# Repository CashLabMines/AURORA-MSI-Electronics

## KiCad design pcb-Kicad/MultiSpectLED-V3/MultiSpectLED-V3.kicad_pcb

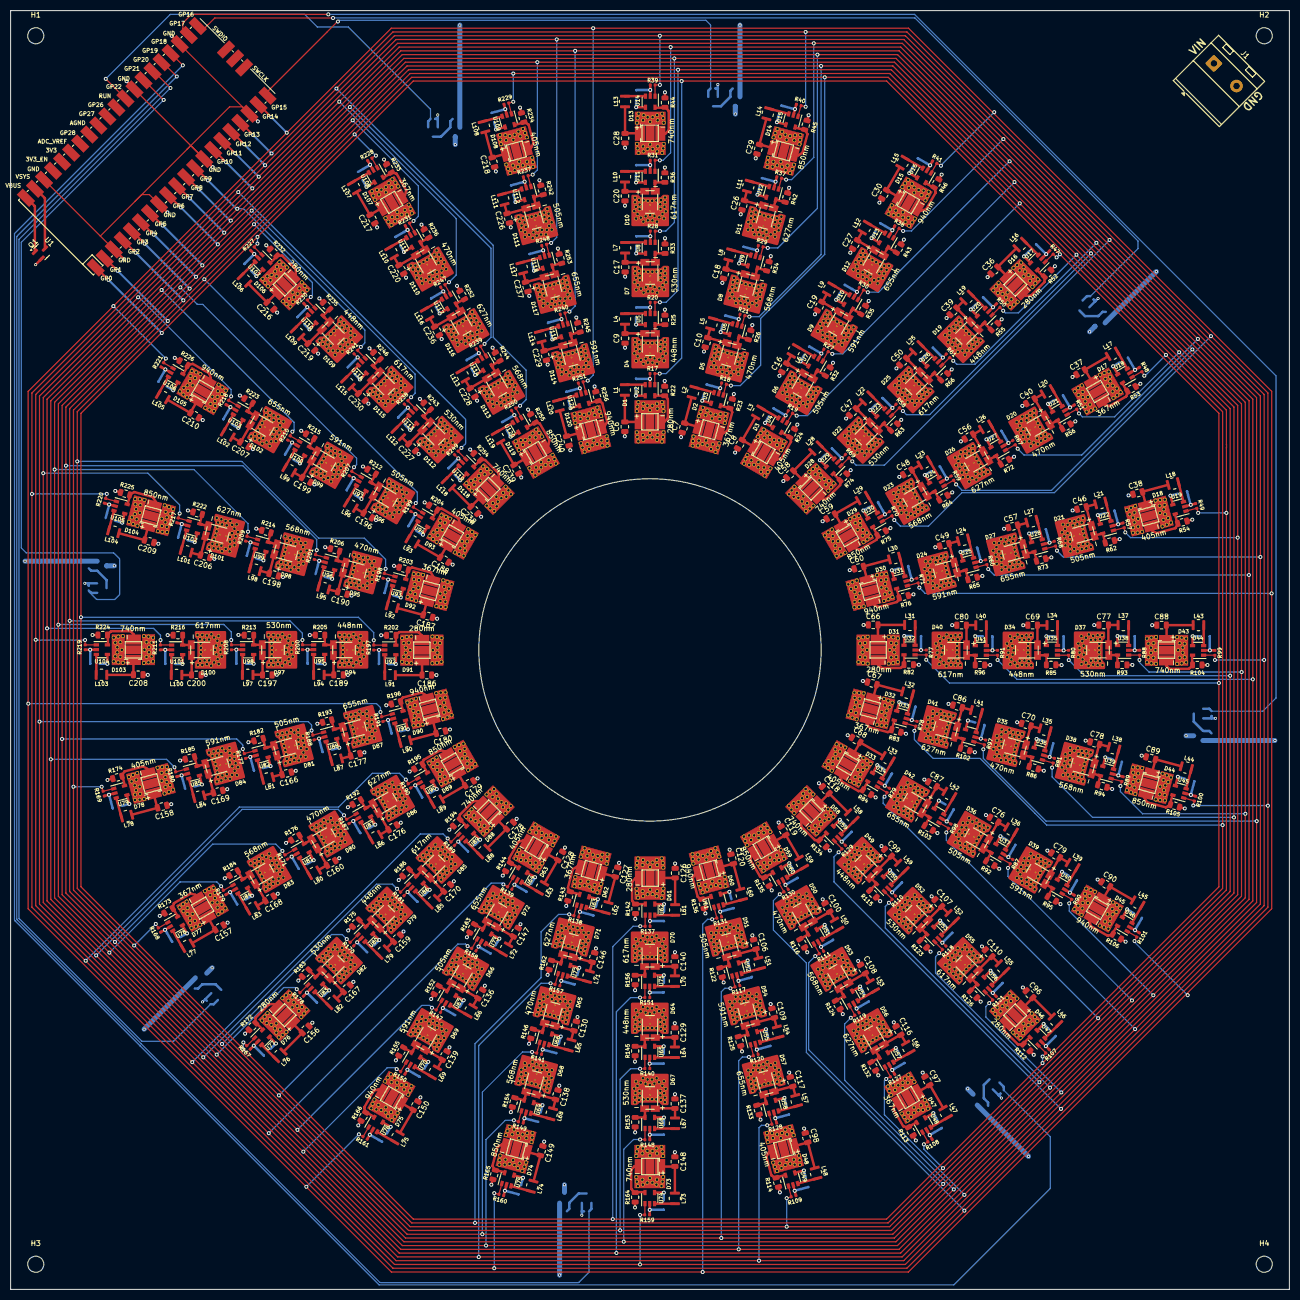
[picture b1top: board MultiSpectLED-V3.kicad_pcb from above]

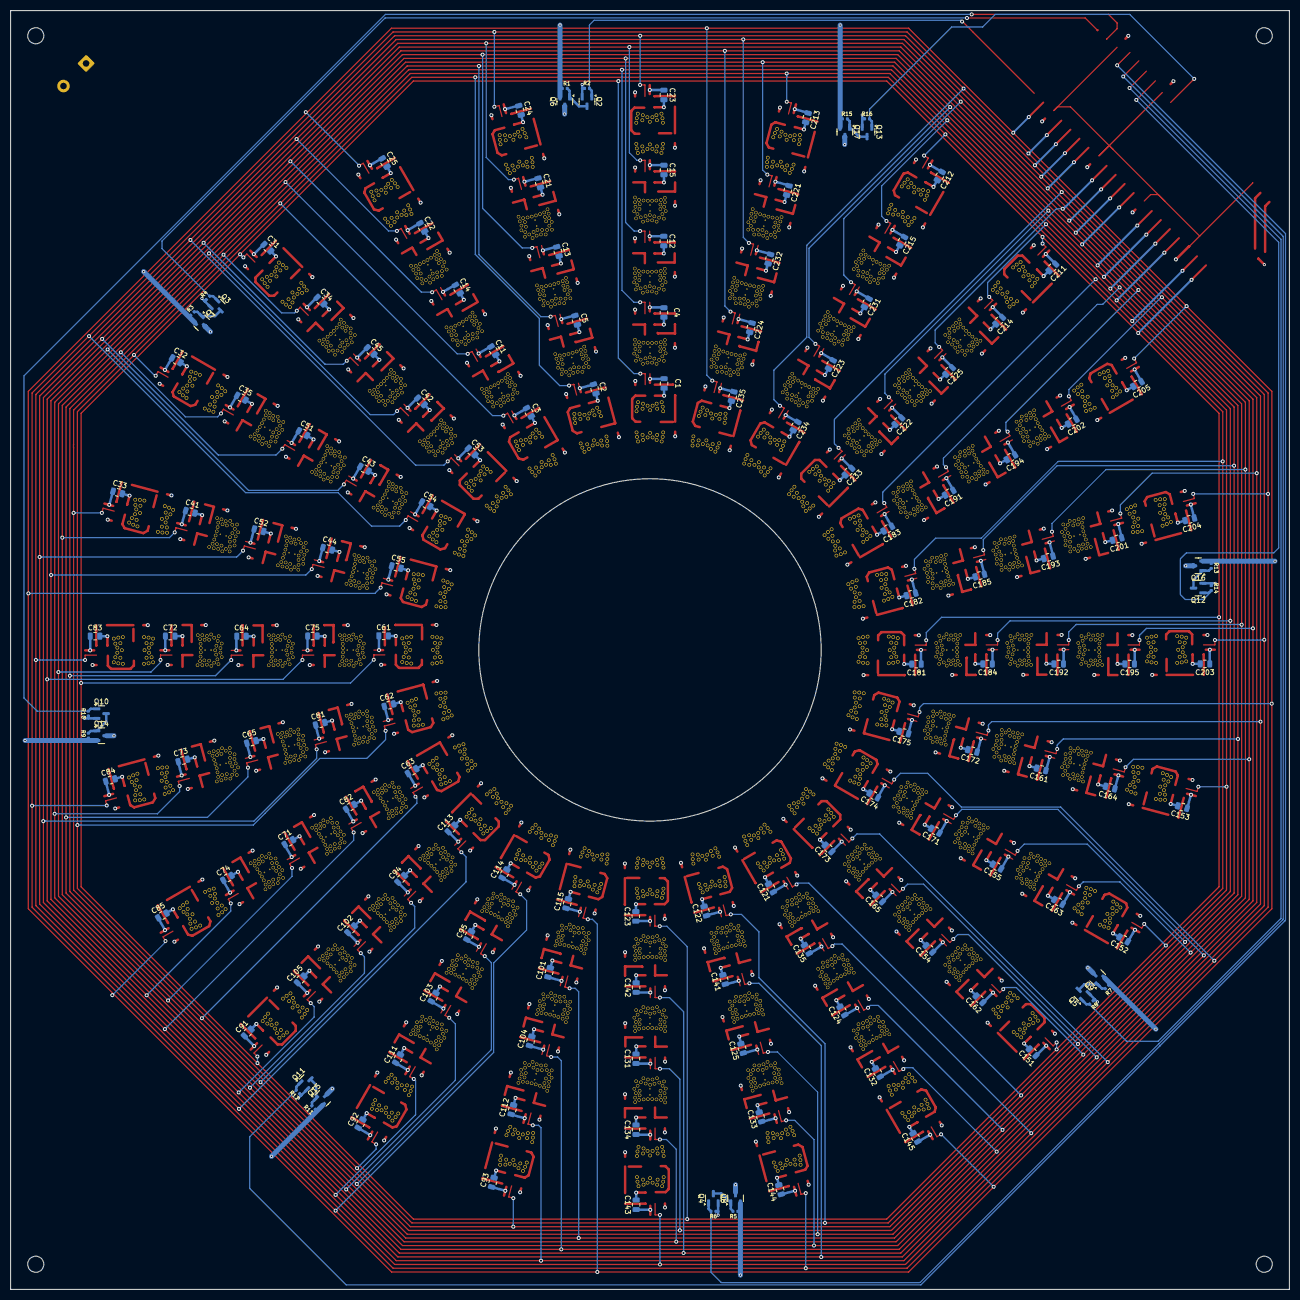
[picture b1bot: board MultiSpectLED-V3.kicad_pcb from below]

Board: 4 copper layers, 254.0 x 254.0 mm, 879 parts (152 on the bottom side), 403 nets.

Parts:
C1, C2, C3, C4, C5, C11, C12, C13, C14, C15, C21, C22, C23, C24, C25, C31, C32, C33, C34, C35, C41, C42, C43, C44, C45, C51, C52, C53, C54, C55, C61, C62, C63, C64, C65, C71, C72, C73, C74, C75, C81, C82, C83, C84, C85, C91, C92, C93, C94, C95, C101, C102, C103, C104, C105, C111, C112, C113, C114, C115, C121, C122, C123, C124, C125, C131, C132, C133, C134, C135, C141, C142, C143, C144, C145, C151, C152, C153, C154, C155, C161, C162, C163, C164, C165, C171, C172, C173, C174, C175, C181, C182, C183, C184, C185, C191, C192, C193, C194, C195, C201, C202, C203, C204, C205, C211, C212, C213, C214, C215, C221, C222, C223, C224, C225, C231, C232, C233, C234, C235: 10uF; C_0805_2012Metric
C6, C7, C8, C9, C10, C16, C17, C18, C19, C20, C26, C27, C28, C29, C30, C36, C37, C38, C39, C40, C46, C47, C48, C49, C50, C56, C57, C58, C59, C60, C66, C67, C68, C69, C70, C76, C77, C78, C79, C80, C86, C87, C88, C89, C90, C96, C97, C98, C99, C100, C106, C107, C108, C109, C110, C116, C117, C118, C119, C120, C126, C127, C128, C129, C130, C136, C137, C138, C139, C140, C146, C147, C148, C149, C150, C156, C157, C158, C159, C160, C166, C167, C168, C169, C170, C176, C177, C178, C179, C180, C186, C187, C188, C189, C190, C196, C197, C198, C199, C200, C206, C207, C208, C209, C210, C216, C217, C218, C219, C220, C226, C227, C228, C229, C230, C236, C237, C238, C239, C240: 1uF; C_0805_2012Metric
D1, D16, D31, D46, D61, D76, D91, D106: 280nm; Luminus_XBT3535
D2, D17, D32, D47, D62, D77, D92, D107: 367nm; SeoulViosys_CUN6GF1A
D3, D18, D33, D48, D63, D78, D93, D108: 405nm; Everlight_ELUA3535
D4, D19, D34, D49, D64, D79, D94, D109: 448nm; LuxeonRebelColor
D5, D20, D35, D50, D65, D80, D95, D110: 470nm; LuxeonRebelColor
D6, D21, D36, D51, D66, D81, D96, D111: 505nm; LuxeonRebelColor
D7, D22, D37, D52, D67, D82, D97, D112: 530nm; LuxeonRebelColor
D8, D23, D38, D53, D68, D83, D98, D113: 568nm; LuxeonRebelColor
D9, D24, D39, D54, D69, D84, D99, D114: 591nm; LuxeonRebelColor
D10, D25, D40, D55, D70, D85, D100, D115: 617nm; LuxeonRebelColor
D11, D26, D41, D56, D71, D86, D101, D116: 627nm; LuxeonRebelColor
D12, D27, D42, D57, D72, D87, D102, D117: 655nm; LuxeonRebelColor
D13, D28, D43, D58, D73, D88, D103, D118: 740nm; QT_Brightek_QBHP684
D14, D29, D44, D59, D74, D89, D104, D119: 850nm; QT_Brightek_QBHP684
D15, D30, D45, D60, D75, D90, D105, D120: 940nm; QT_Brightek_QBHP684
H1, H2, H3, H4: M3 Mounting Hole; MountingHole_3.2mm_M3
J1: Screw_Terminal_01x02; TerminalBlock_MetzConnect_Type701_RT11L02HGLU_1x02_P6.35mm_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
L1, L2, L3, L4, L5, L6, L7, L8, L9, L10, L11, L12, L13, L14, L15, L16, L17, L18, L19, L20, L21, L22, L23, L24, L25, L26, L27, L28, L29, L30, L31, L32, L33, L34, L35, L36, L37, L38, L39, L40, L41, L42, L43, L44, L45, L46, L47, L48, L49, L50, L51, L52, L53, L54, L55, L56, L57, L58, L59, L60, L61, L62, L63, L64, L65, L66, L67, L68, L69, L70, L71, L72, L73, L74, L75, L76, L77, L78, L79, L80, L81, L82, L83, L84, L85, L86, L87, L88, L89, L90, L91, L92, L93, L94, L95, L96, L97, L98, L99, L100, L101, L102, L103, L104, L105, L106, L107, L108, L109, L110, L111, L112, L113, L114, L115, L116, L117, L118, L119, L120: 4.7u; L_1007_2518Metric
Q1, Q6, Q7, Q8, Q9, Q14, Q15, Q16, Q17: DMG2301L; SOT-23
Q2, Q3, Q4, Q5, Q10, Q11, Q12, Q13: BC817; SOT-23
R1, R2, R3, R4, R5, R6, R7, R8, R9, R10, R11, R12, R13, R14, R15, R16, R17, R18, R19, R20, R21, R27, R28, R29, R30, R31, R37, R38, R39, R40, R41, R47, R48, R49, R50, R51, R57, R58, R59, R60, R61, R67, R68, R69, R70, R71, R77, R78, R79, R80, R81, R87, R88, R89, R90, R91, R97, R98, R99, R100, R101, R107, R108, R109, R110, R111, R117, R118, R119, R120, R121, R127, R128, R129, R130, R131, R137, R138, R139, R140, R141, R147, R148, R149, R150, R151, R157, R158, R159, R160, R161, R167, R168, R169, R170, R171, R177, R178, R179, R180, R181, R187, R188, R189, R190, R191, R197, R198, R199, R200, R201, R207, R208, R209, R210, R211, R217, R218, R219, R220, R221, R227, R228, R229, R230, R231, R237, R238, R239, R240, R241, R247, R248, R249, R250, R251: 100K; R_0402_1005Metric
R22, R23, R24, R25, R26, R32, R33, R34, R35, R36, R42, R43, R44, R45, R46, R52, R53, R54, R55, R56, R62, R63, R64, R65, R66, R72, R73, R74, R75, R76, R82, R83, R84, R85, R86, R92, R93, R94, R95, R96, R102, R103, R104, R105, R106, R112, R113, R114, R115, R116, R122, R123, R124, R125, R126, R132, R133, R134, R135, R136, R142, R143, R144, R145, R146, R152, R153, R154, R155, R156, R162, R163, R164, R165, R166, R172, R173, R174, R175, R176, R182, R183, R184, R185, R186, R192, R193, R194, R195, R196, R202, R203, R204, R205, R206, R212, R213, R214, R215, R216, R222, R223, R224, R225, R226, R232, R233, R234, R235, R236, R242, R243, R244, R245, R246, R252, R253, R254, R255, R256: 0.2; R_0805_2012Metric
U1: RaspberryPi_Pico2_SM; RPi_Pico_SMD_SM
U2, U3, U4, U5, U6, U7, U8, U9, U10, U11, U12, U13, U14, U15, U16, U17, U18, U19, U20, U21, U22, U23, U24, U25, U26, U27, U28, U29, U30, U31, U32, U33, U34, U35, U36, U37, U38, U39, U40, U41, U42, U43, U44, U45, U46, U47, U48, U49, U50, U51, U52, U53, U54, U55, U56, U57, U58, U59, U60, U61, U62, U63, U64, U65, U66, U67, U68, U69, U70, U71, U72, U73, U74, U75, U76, U77, U78, U79, U80, U81, U82, U83, U84, U85, U86, U87, U88, U89, U90, U91, U92, U93, U94, U95, U96, U97, U98, U99, U100, U101, U102, U103, U104, U105, U106, U107, U108, U109, U110, U111, U112, U113, U114, U115, U116, U117, U118, U119, U120, U121: PAM2804; SOT-23-5

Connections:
+5V: J1.1, Q1.2 (S), Q6.2 (S), Q7.2 (S), Q8.2 (S), Q9.2 (S), Q14.2 (S), Q15.2 (S), Q16.2 (S), Q17.2 (S), R1.1, R3.1, R5.1, R7.1, R9.1, R11.1, R13.1, R15.1
/LED Column 1/VCC: C1.2, C2.2, C3.2, C4.2, C5.2, C11.2, C12.2, C13.2, C14.2, C15.2, C21.2, C22.2, C23.2, C24.2, C25.2, Q6.3 (D), U2.4 (VIN), U3.4 (VIN), U4.4 (VIN), U5.4 (VIN), U6.4 (VIN), U7.4 (VIN), U8.4 (VIN), U9.4 (VIN), U10.4 (VIN), U11.4 (VIN), U12.4 (VIN), U13.4 (VIN), U14.4 (VIN), U15.4 (VIN), U16.4 (VIN)
/LED Column 2/VCC: C31.2, C32.2, C33.2, C34.2, C35.2, C41.2, C42.2, C43.2, C44.2, C45.2, C51.2, C52.2, C53.2, C54.2, C55.2, Q7.3 (D), U17.4 (VIN), U18.4 (VIN), U19.4 (VIN), U20.4 (VIN), U21.4 (VIN), U22.4 (VIN), U23.4 (VIN), U24.4 (VIN), U25.4 (VIN), U26.4 (VIN), U27.4 (VIN), U28.4 (VIN), U29.4 (VIN), U30.4 (VIN), U31.4 (VIN)
/LED Column 3/VCC: C61.2, C62.2, C63.2, C64.2, C65.2, C71.2, C72.2, C73.2, C74.2, C75.2, C81.2, C82.2, C83.2, C84.2, C85.2, Q14.3 (D), U32.4 (VIN), U33.4 (VIN), U34.4 (VIN), U35.4 (VIN), U36.4 (VIN), U37.4 (VIN), U38.4 (VIN), U39.4 (VIN), U40.4 (VIN), U41.4 (VIN), U42.4 (VIN), U43.4 (VIN), U44.4 (VIN), U45.4 (VIN), U46.4 (VIN)
/LED Column 4/VCC: C91.2, C92.2, C93.2, C94.2, C95.2, C101.2, C102.2, C103.2, C104.2, C105.2, C111.2, C112.2, C113.2, C114.2, C115.2, Q15.3 (D), U47.4 (VIN), U48.4 (VIN), U49.4 (VIN), U50.4 (VIN), U51.4 (VIN), U52.4 (VIN), U53.4 (VIN), U54.4 (VIN), U55.4 (VIN), U56.4 (VIN), U57.4 (VIN), U58.4 (VIN), U59.4 (VIN), U60.4 (VIN), U61.4 (VIN)
/LED Column 5/VCC: C121.2, C122.2, C123.2, C124.2, C125.2, C131.2, C132.2, C133.2, C134.2, C135.2, C141.2, C142.2, C143.2, C144.2, C145.2, Q8.3 (D), U62.4 (VIN), U63.4 (VIN), U64.4 (VIN), U65.4 (VIN), U66.4 (VIN), U67.4 (VIN), U68.4 (VIN), U69.4 (VIN), U70.4 (VIN), U71.4 (VIN), U72.4 (VIN), U73.4 (VIN), U74.4 (VIN), U75.4 (VIN), U76.4 (VIN)
/LED Column 6/VCC: C151.2, C152.2, C153.2, C154.2, C155.2, C161.2, C162.2, C163.2, C164.2, C165.2, C171.2, C172.2, C173.2, C174.2, C175.2, Q9.3 (D), U77.4 (VIN), U78.4 (VIN), U79.4 (VIN), U80.4 (VIN), U81.4 (VIN), U82.4 (VIN), U83.4 (VIN), U84.4 (VIN), U85.4 (VIN), U86.4 (VIN), U87.4 (VIN), U88.4 (VIN), U89.4 (VIN), U90.4 (VIN), U91.4 (VIN)
/LED Column 7/VCC: C181.2, C182.2, C183.2, C184.2, C185.2, C191.2, C192.2, C193.2, C194.2, C195.2, C201.2, C202.2, C203.2, C204.2, C205.2, Q16.3 (D), U92.4 (VIN), U93.4 (VIN), U94.4 (VIN), U95.4 (VIN), U96.4 (VIN), U97.4 (VIN), U98.4 (VIN), U99.4 (VIN), U100.4 (VIN), U101.4 (VIN), U102.4 (VIN), U103.4 (VIN), U104.4 (VIN), U105.4 (VIN), U106.4 (VIN)
/LED Column 8/VCC: C211.2, C212.2, C213.2, C214.2, C215.2, C221.2, C222.2, C223.2, C224.2, C225.2, C231.2, C232.2, C233.2, C234.2, C235.2, Q17.3 (D), U107.4 (VIN), U108.4 (VIN), U109.4 (VIN), U110.4 (VIN), U111.4 (VIN), U112.4 (VIN), U113.4 (VIN), U114.4 (VIN), U115.4 (VIN), U116.4 (VIN), U117.4 (VIN), U118.4 (VIN), U119.4 (VIN), U120.4 (VIN), U121.4 (VIN)
/PWM_280nm: R17.1, R47.1, R77.1, R107.1, R137.1, R167.1, R197.1, R227.1, U1.1 (GPIO0), U2.1 (EN), U17.1 (EN), U32.1 (EN), U47.1 (EN), U62.1 (EN), U77.1 (EN), U92.1 (EN), U107.1 (EN)
/PWM_367nm: R18.1, R48.1, R78.1, R108.1, R138.1, R168.1, R198.1, R228.1, U1.2 (GPIO1), U3.1 (EN), U18.1 (EN), U33.1 (EN), U48.1 (EN), U63.1 (EN), U78.1 (EN), U93.1 (EN), U108.1 (EN)
/PWM_405nm: R19.1, R49.1, R79.1, R109.1, R139.1, R169.1, R199.1, R229.1, U1.4 (GPIO2), U4.1 (EN), U19.1 (EN), U34.1 (EN), U49.1 (EN), U64.1 (EN), U79.1 (EN), U94.1 (EN), U109.1 (EN)
/PWM_448nm: R20.1, R50.1, R80.1, R110.1, R140.1, R170.1, R200.1, R230.1, U1.5 (GPIO3), U5.1 (EN), U20.1 (EN), U35.1 (EN), U50.1 (EN), U65.1 (EN), U80.1 (EN), U95.1 (EN), U110.1 (EN)
/PWM_470nm: R21.1, R51.1, R81.1, R111.1, R141.1, R171.1, R201.1, R231.1, U1.6 (GPIO4), U6.1 (EN), U21.1 (EN), U36.1 (EN), U51.1 (EN), U66.1 (EN), U81.1 (EN), U96.1 (EN), U111.1 (EN)
/PWM_505nm: R27.1, R57.1, R87.1, R117.1, R147.1, R177.1, R207.1, R237.1, U1.7 (GPIO5), U7.1 (EN), U22.1 (EN), U37.1 (EN), U52.1 (EN), U67.1 (EN), U82.1 (EN), U97.1 (EN), U112.1 (EN)
/PWM_530nm: R28.1, R58.1, R88.1, R118.1, R148.1, R178.1, R208.1, R238.1, U1.9 (GPIO6), U8.1 (EN), U23.1 (EN), U38.1 (EN), U53.1 (EN), U68.1 (EN), U83.1 (EN), U98.1 (EN), U113.1 (EN)
/PWM_568nm: R29.1, R59.1, R89.1, R119.1, R149.1, R179.1, R209.1, R239.1, U1.10 (GPIO7), U9.1 (EN), U24.1 (EN), U39.1 (EN), U54.1 (EN), U69.1 (EN), U84.1 (EN), U99.1 (EN), U114.1 (EN)
/PWM_591nm: R30.1, R60.1, R90.1, R120.1, R150.1, R180.1, R210.1, R240.1, U1.11 (GPIO8), U10.1 (EN), U25.1 (EN), U40.1 (EN), U55.1 (EN), U70.1 (EN), U85.1 (EN), U100.1 (EN), U115.1 (EN)
/PWM_617nm: R31.1, R61.1, R91.1, R121.1, R151.1, R181.1, R211.1, R241.1, U1.12 (GPIO9), U11.1 (EN), U26.1 (EN), U41.1 (EN), U56.1 (EN), U71.1 (EN), U86.1 (EN), U101.1 (EN), U116.1 (EN)
/PWM_627nm: R37.1, R67.1, R97.1, R127.1, R157.1, R187.1, R217.1, R247.1, U1.14 (GPIO10), U12.1 (EN), U27.1 (EN), U42.1 (EN), U57.1 (EN), U72.1 (EN), U87.1 (EN), U102.1 (EN), U117.1 (EN)
/PWM_655nm: R38.1, R68.1, R98.1, R128.1, R158.1, R188.1, R218.1, R248.1, U1.15 (GPIO11), U13.1 (EN), U28.1 (EN), U43.1 (EN), U58.1 (EN), U73.1 (EN), U88.1 (EN), U103.1 (EN), U118.1 (EN)
/PWM_740nm: R39.1, R69.1, R99.1, R129.1, R159.1, R189.1, R219.1, R249.1, U1.16 (GPIO12), U14.1 (EN), U29.1 (EN), U44.1 (EN), U59.1 (EN), U74.1 (EN), U89.1 (EN), U104.1 (EN), U119.1 (EN)
/PWM_850nm: R40.1, R70.1, R100.1, R130.1, R160.1, R190.1, R220.1, R250.1, U1.17 (GPIO13), U15.1 (EN), U30.1 (EN), U45.1 (EN), U60.1 (EN), U75.1 (EN), U90.1 (EN), U105.1 (EN), U120.1 (EN)
/PWM_940nm: R41.1, R71.1, R101.1, R131.1, R161.1, R191.1, R221.1, R251.1, U1.19 (GPIO14), U16.1 (EN), U31.1 (EN), U46.1 (EN), U61.1 (EN), U76.1 (EN), U91.1 (EN), U106.1 (EN), U121.1 (EN)
/PWR_ENABLE1: Q2.1 (B), R2.1, U1.20 (GPIO15)
/PWR_ENABLE2: Q3.1 (B), R4.1, U1.21 (GPIO16)
/PWR_ENABLE3: Q10.1 (B), R10.1, U1.22 (GPIO17)
/PWR_ENABLE4: Q11.1 (B), R12.1, U1.24 (GPIO18)
/PWR_ENABLE5: Q4.1 (B), R6.1, U1.25 (GPIO19)
/PWR_ENABLE6: Q5.1 (B), R8.1, U1.26 (GPIO20)
/PWR_ENABLE7: Q12.1 (B), R14.1, U1.27 (GPIO21)
/PWR_ENABLE8: Q13.1 (B), R16.1, U1.29 (GPIO22)
GND: C1.1, C2.1, C3.1, C4.1, C5.1, C6.1, C7.1, C8.1, C9.1, C10.1, C11.1, C12.1, C13.1, C14.1, C15.1, C16.1, C17.1, C18.1, C19.1, C20.1, C21.1, C22.1, C23.1, C24.1, C25.1, C26.1, C27.1, C28.1, C29.1, C30.1, C31.1, C32.1, C33.1, C34.1, C35.1, C36.1, C37.1, C38.1, C39.1, C40.1, C41.1, C42.1, C43.1, C44.1, C45.1, C46.1, C47.1, C48.1, C49.1, C50.1, C51.1, C52.1, C53.1, C54.1, C55.1, C56.1, C57.1, C58.1, C59.1, C60.1, C61.1, C62.1, C63.1, C64.1, C65.1, C66.1, C67.1, C68.1, C69.1, C70.1, C71.1, C72.1, C73.1, C74.1, C75.1, C76.1, C77.1, C78.1, C79.1, C80.1, C81.1, C82.1, C83.1, C84.1, C85.1, C86.1, C87.1, C88.1, C89.1, C90.1, C91.1, C92.1, C93.1, C94.1, C95.1, C96.1, C97.1, C98.1, C99.1, C100.1, C101.1, C102.1, C103.1, C104.1, C105.1, C106.1, C107.1, C108.1, C109.1, C110.1, C111.1, C112.1, C113.1, C114.1, C115.1, C116.1, C117.1, C118.1, C119.1, C120.1, C121.1, C122.1, C123.1, C124.1, C125.1, C126.1, C127.1, C128.1, C129.1, C130.1, C131.1, C132.1, C133.1, C134.1, C135.1, C136.1, C137.1, C138.1, C139.1, C140.1, C141.1, C142.1, C143.1, C144.1, C145.1, C146.1, C147.1, C148.1, C149.1, C150.1, C151.1, C152.1, C153.1, C154.1, C155.1, C156.1, C157.1, C158.1, C159.1, C160.1, C161.1, C162.1, C163.1, C164.1, C165.1, C166.1, C167.1, C168.1, C169.1, C170.1, C171.1, C172.1, C173.1, C174.1, C175.1, C176.1, C177.1, C178.1, C179.1, C180.1, C181.1, C182.1, C183.1, C184.1, C185.1, C186.1, C187.1, C188.1, C189.1, C190.1, C191.1, C192.1, C193.1, C194.1, C195.1, C196.1, C197.1, C198.1, C199.1, C200.1, C201.1, C202.1, C203.1, C204.1, C205.1, C206.1, C207.1, C208.1, C209.1, C210.1, C211.1, C212.1, C213.1, C214.1, C215.1, C216.1, C217.1, C218.1, C219.1, C220.1, C221.1, C222.1, C223.1, C224.1, C225.1, C226.1, C227.1, C228.1, C229.1, C230.1, C231.1, C232.1, C233.1, C234.1, C235.1, C236.1, C237.1, C238.1, C239.1, C240.1, D1.3 (PAD), D2.3 (PAD), D3.3 (PAD), D4.3 (PAD), D5.3 (PAD), D6.3 (PAD), D7.3 (PAD), D8.3 (PAD), D9.3 (PAD), D10.3 (PAD), D11.3 (PAD), D12.3 (PAD), D13.3 (PAD), D14.3 (PAD), D15.3 (PAD), D16.3 (PAD), D17.3 (PAD), D18.3 (PAD), D19.3 (PAD), D20.3 (PAD), D21.3 (PAD), D22.3 (PAD), D23.3 (PAD), D24.3 (PAD), D25.3 (PAD), D26.3 (PAD), D27.3 (PAD), D28.3 (PAD), D29.3 (PAD), D30.3 (PAD), D31.3 (PAD), D32.3 (PAD), D33.3 (PAD), D34.3 (PAD), D35.3 (PAD), D36.3 (PAD), D37.3 (PAD), D38.3 (PAD), D39.3 (PAD), D40.3 (PAD), D41.3 (PAD), D42.3 (PAD), D43.3 (PAD), D44.3 (PAD), D45.3 (PAD), D46.3 (PAD), D47.3 (PAD), D48.3 (PAD), D49.3 (PAD), D50.3 (PAD), D51.3 (PAD), D52.3 (PAD), D53.3 (PAD), D54.3 (PAD), D55.3 (PAD), D56.3 (PAD), D57.3 (PAD), D58.3 (PAD), D59.3 (PAD), D60.3 (PAD), D61.3 (PAD), D62.3 (PAD), D63.3 (PAD), D64.3 (PAD), D65.3 (PAD), D66.3 (PAD), D67.3 (PAD), D68.3 (PAD), D69.3 (PAD), D70.3 (PAD), D71.3 (PAD), D72.3 (PAD), D73.3 (PAD), D74.3 (PAD), D75.3 (PAD), D76.3 (PAD), D77.3 (PAD), D78.3 (PAD), D79.3 (PAD), D80.3 (PAD), D81.3 (PAD), D82.3 (PAD), D83.3 (PAD), D84.3 (PAD), D85.3 (PAD), D86.3 (PAD), D87.3 (PAD), D88.3 (PAD), D89.3 (PAD), D90.3 (PAD), D91.3 (PAD), D92.3 (PAD), D93.3 (PAD), D94.3 (PAD), D95.3 (PAD), D96.3 (PAD), D97.3 (PAD), D98.3 (PAD), D99.3 (PAD), D100.3 (PAD), D101.3 (PAD), D102.3 (PAD), D103.3 (PAD), D104.3 (PAD), D105.3 (PAD), D106.3 (PAD), D107.3 (PAD), D108.3 (PAD), D109.3 (PAD), D110.3 (PAD), D111.3 (PAD), D112.3 (PAD), D113.3 (PAD), D114.3 (PAD), D115.3 (PAD), D116.3 (PAD), D117.3 (PAD), D118.3 (PAD), D119.3 (PAD), D120.3 (PAD), J1.2, Q2.2 (E), Q3.2 (E), Q4.2 (E), Q5.2 (E), Q10.2 (E), Q11.2 (E), Q12.2 (E), Q13.2 (E), R2.2, R4.2, R6.2, R8.2, R10.2, R12.2, R14.2, R16.2, R17.2, R18.2, R19.2, R20.2, R21.2, R22.2, R23.2, R24.2, R25.2, R26.2, R27.2, R28.2, R29.2, R30.2, R31.2, R32.2, R33.2, R34.2, R35.2, R36.2, R37.2, R38.2, R39.2, R40.2, R41.2, R42.2, R43.2, R44.2, R45.2, R46.2, R47.2, R48.2, R49.2, R50.2, R51.2, R52.2, R53.2, R54.2, R55.2, R56.2, R57.2, R58.2, R59.2, R60.2, R61.2, R62.2, R63.2, R64.2, R65.2, R66.2, R67.2, R68.2, R69.2, R70.2, R71.2, R72.2, R73.2, R74.2, R75.2, R76.2, R77.2, R78.2, R79.2, R80.2, R81.2, R82.2, R83.2, R84.2, R85.2, R86.2, R87.2, R88.2, R89.2, R90.2, R91.2, R92.2, R93.2, R94.2, R95.2, R96.2, R97.2, R98.2, R99.2, R100.2, R101.2, R102.2, R103.2, R104.2, R105.2, R106.2, R107.2, R108.2, R109.2, R110.2, R111.2, R112.2, R113.2, R114.2, R115.2, R116.2, R117.2, R118.2, R119.2, R120.2, R121.2, R122.2, R123.2, R124.2, R125.2, R126.2, R127.2, R128.2, R129.2, R130.2, R131.2, R132.2, R133.2, R134.2, R135.2, R136.2, R137.2, R138.2, R139.2, R140.2, R141.2, R142.2, R143.2, R144.2, R145.2, R146.2, R147.2, R148.2, R149.2, R150.2, R151.2, R152.2, R153.2, R154.2, R155.2, R156.2, R157.2, R158.2, R159.2, R160.2, R161.2, R162.2, R163.2, R164.2, R165.2, R166.2, R167.2, R168.2, R169.2, R170.2, R171.2, R172.2, R173.2, R174.2, R175.2, R176.2, R177.2, R178.2, R179.2, R180.2, R181.2, R182.2, R183.2, R184.2, R185.2, R186.2, R187.2, R188.2, R189.2, R190.2, R191.2, R192.2, R193.2, R194.2, R195.2, R196.2, R197.2, R198.2, R199.2, R200.2, R201.2, R202.2, R203.2, R204.2, R205.2, R206.2, R207.2, R208.2, R209.2, R210.2, R211.2, R212.2, R213.2, R214.2, R215.2, R216.2, R217.2, R218.2, R219.2, R220.2, R221.2, R222.2, R223.2, R224.2, R225.2, R226.2, R227.2, R228.2, R229.2, R230.2, R231.2, R232.2, R233.2, R234.2, R235.2, R236.2, R237.2, R238.2, R239.2, R240.2, R241.2, R242.2, R243.2, R244.2, R245.2, R246.2, R247.2, R248.2, R249.2, R250.2, R251.2, R252.2, R253.2, R254.2, R255.2, R256.2, U1.3 (GND), U1.8 (GND), U1.13 (GND), U1.18 (GND), U1.23 (GND), U1.28 (GND), U1.38 (GND), U2.2 (GND), U3.2 (GND), U4.2 (GND), U5.2 (GND), U6.2 (GND), U7.2 (GND), U8.2 (GND), U9.2 (GND), U10.2 (GND), U11.2 (GND), U12.2 (GND), U13.2 (GND), U14.2 (GND), U15.2 (GND), U16.2 (GND), U17.2 (GND), U18.2 (GND), U19.2 (GND), U20.2 (GND), U21.2 (GND), U22.2 (GND), U23.2 (GND), U24.2 (GND), U25.2 (GND), U26.2 (GND), U27.2 (GND), U28.2 (GND), U29.2 (GND), U30.2 (GND), U31.2 (GND), U32.2 (GND), U33.2 (GND), U34.2 (GND), U35.2 (GND), U36.2 (GND), U37.2 (GND), U38.2 (GND), U39.2 (GND), U40.2 (GND), U41.2 (GND), U42.2 (GND), U43.2 (GND), U44.2 (GND), U45.2 (GND), U46.2 (GND), U47.2 (GND), U48.2 (GND), U49.2 (GND), U50.2 (GND), U51.2 (GND), U52.2 (GND), U53.2 (GND), U54.2 (GND), U55.2 (GND), U56.2 (GND), U57.2 (GND), U58.2 (GND), U59.2 (GND), U60.2 (GND), U61.2 (GND), U62.2 (GND), U63.2 (GND), U64.2 (GND), U65.2 (GND), U66.2 (GND), U67.2 (GND), U68.2 (GND), U69.2 (GND), U70.2 (GND), U71.2 (GND), U72.2 (GND), U73.2 (GND), U74.2 (GND), U75.2 (GND), U76.2 (GND), U77.2 (GND), U78.2 (GND), U79.2 (GND), U80.2 (GND), U81.2 (GND), U82.2 (GND), U83.2 (GND), U84.2 (GND), U85.2 (GND), U86.2 (GND), U87.2 (GND), U88.2 (GND), U89.2 (GND), U90.2 (GND), U91.2 (GND), U92.2 (GND), U93.2 (GND), U94.2 (GND), U95.2 (GND), U96.2 (GND), U97.2 (GND), U98.2 (GND), U99.2 (GND), U100.2 (GND), U101.2 (GND), U102.2 (GND), U103.2 (GND), U104.2 (GND), U105.2 (GND), U106.2 (GND), U107.2 (GND), U108.2 (GND), U109.2 (GND), U110.2 (GND), U111.2 (GND), U112.2 (GND), U113.2 (GND), U114.2 (GND), U115.2 (GND), U116.2 (GND), U117.2 (GND), U118.2 (GND), U119.2 (GND), U120.2 (GND), U121.2 (GND)
unnamed: C6.2, D1.2 (A), L1.2
unnamed: D1.1 (K), R22.1, U2.5 (FB)
unnamed: C7.2, D2.2 (A), L2.2
unnamed: D2.1 (K), R23.1, U3.5 (FB)
unnamed: C8.2, D3.1 (A), L3.2
unnamed: D3.2 (K), R24.1, U4.5 (FB)
unnamed: C9.2, D4.2 (A), L4.2
unnamed: D4.1 (K), R25.1, U5.5 (FB)
unnamed: C10.2, D5.2 (A), L5.2
unnamed: D5.1 (K), R26.1, U6.5 (FB)
unnamed: C16.2, D6.2 (A), L6.2
unnamed: D6.1 (K), R32.1, U7.5 (FB)
unnamed: C17.2, D7.2 (A), L7.2
unnamed: D7.1 (K), R33.1, U8.5 (FB)
unnamed: C18.2, D8.2 (A), L8.2
unnamed: D8.1 (K), R34.1, U9.5 (FB)
unnamed: C19.2, D9.2 (A), L9.2
unnamed: D9.1 (K), R35.1, U10.5 (FB)
unnamed: C20.2, D10.2 (A), L10.2
unnamed: D10.1 (K), R36.1, U11.5 (FB)
unnamed: C26.2, D11.2 (A), L11.2
unnamed: D11.1 (K), R42.1, U12.5 (FB)
unnamed: C27.2, D12.2 (A), L12.2
unnamed: D12.1 (K), R43.1, U13.5 (FB)
unnamed: C28.2, D13.1 (A), L13.2
unnamed: D13.2 (K), R44.1, U14.5 (FB)
unnamed: C29.2, D14.1 (A), L14.2
unnamed: D14.2 (K), R45.1, U15.5 (FB)
unnamed: C30.2, D15.1 (A), L15.2
unnamed: D15.2 (K), R46.1, U16.5 (FB)
unnamed: C36.2, D16.2 (A), L16.2
unnamed: D16.1 (K), R52.1, U17.5 (FB)
unnamed: C37.2, D17.2 (A), L17.2
unnamed: D17.1 (K), R53.1, U18.5 (FB)
unnamed: C38.2, D18.1 (A), L18.2
unnamed: D18.2 (K), R54.1, U19.5 (FB)
unnamed: C39.2, D19.2 (A), L19.2
unnamed: D19.1 (K), R55.1, U20.5 (FB)
unnamed: C40.2, D20.2 (A), L20.2
unnamed: D20.1 (K), R56.1, U21.5 (FB)
unnamed: C46.2, D21.2 (A), L21.2
unnamed: D21.1 (K), R62.1, U22.5 (FB)
unnamed: C47.2, D22.2 (A), L22.2
unnamed: D22.1 (K), R63.1, U23.5 (FB)
unnamed: C48.2, D23.2 (A), L23.2
unnamed: D23.1 (K), R64.1, U24.5 (FB)
unnamed: C49.2, D24.2 (A), L24.2
unnamed: D24.1 (K), R65.1, U25.5 (FB)
unnamed: C50.2, D25.2 (A), L25.2
unnamed: D25.1 (K), R66.1, U26.5 (FB)
unnamed: C56.2, D26.2 (A), L26.2
unnamed: D26.1 (K), R72.1, U27.5 (FB)
unnamed: C57.2, D27.2 (A), L27.2
unnamed: D27.1 (K), R73.1, U28.5 (FB)
unnamed: C58.2, D28.1 (A), L28.2
unnamed: D28.2 (K), R74.1, U29.5 (FB)
unnamed: C59.2, D29.1 (A), L29.2
unnamed: D29.2 (K), R75.1, U30.5 (FB)
unnamed: C60.2, D30.1 (A), L30.2
unnamed: D30.2 (K), R76.1, U31.5 (FB)
unnamed: C66.2, D31.2 (A), L31.2
unnamed: D31.1 (K), R82.1, U32.5 (FB)
unnamed: C67.2, D32.2 (A), L32.2
unnamed: D32.1 (K), R83.1, U33.5 (FB)
unnamed: C68.2, D33.1 (A), L33.2
unnamed: D33.2 (K), R84.1, U34.5 (FB)
unnamed: C69.2, D34.2 (A), L34.2
unnamed: D34.1 (K), R85.1, U35.5 (FB)
unnamed: C70.2, D35.2 (A), L35.2
unnamed: D35.1 (K), R86.1, U36.5 (FB)
unnamed: C76.2, D36.2 (A), L36.2
unnamed: D36.1 (K), R92.1, U37.5 (FB)
unnamed: C77.2, D37.2 (A), L37.2
unnamed: D37.1 (K), R93.1, U38.5 (FB)
unnamed: C78.2, D38.2 (A), L38.2
unnamed: D38.1 (K), R94.1, U39.5 (FB)
unnamed: C79.2, D39.2 (A), L39.2
unnamed: D39.1 (K), R95.1, U40.5 (FB)
unnamed: C80.2, D40.2 (A), L40.2
unnamed: D40.1 (K), R96.1, U41.5 (FB)
unnamed: C86.2, D41.2 (A), L41.2
unnamed: D41.1 (K), R102.1, U42.5 (FB)
unnamed: C87.2, D42.2 (A), L42.2
unnamed: D42.1 (K), R103.1, U43.5 (FB)
unnamed: C88.2, D43.1 (A), L43.2
unnamed: D43.2 (K), R104.1, U44.5 (FB)
unnamed: C89.2, D44.1 (A), L44.2
unnamed: D44.2 (K), R105.1, U45.5 (FB)
unnamed: C90.2, D45.1 (A), L45.2
unnamed: D45.2 (K), R106.1, U46.5 (FB)
unnamed: C96.2, D46.2 (A), L46.2
unnamed: D46.1 (K), R112.1, U47.5 (FB)
unnamed: C97.2, D47.2 (A), L47.2
unnamed: D47.1 (K), R113.1, U48.5 (FB)
unnamed: C98.2, D48.1 (A), L48.2
unnamed: D48.2 (K), R114.1, U49.5 (FB)
unnamed: C99.2, D49.2 (A), L49.2
unnamed: D49.1 (K), R115.1, U50.5 (FB)
unnamed: C100.2, D50.2 (A), L50.2
unnamed: D50.1 (K), R116.1, U51.5 (FB)
unnamed: C106.2, D51.2 (A), L51.2
unnamed: D51.1 (K), R122.1, U52.5 (FB)
unnamed: C107.2, D52.2 (A), L52.2
unnamed: D52.1 (K), R123.1, U53.5 (FB)
unnamed: C108.2, D53.2 (A), L53.2
unnamed: D53.1 (K), R124.1, U54.5 (FB)
unnamed: C109.2, D54.2 (A), L54.2
unnamed: D54.1 (K), R125.1, U55.5 (FB)
unnamed: C110.2, D55.2 (A), L55.2
unnamed: D55.1 (K), R126.1, U56.5 (FB)
unnamed: C116.2, D56.2 (A), L56.2
unnamed: D56.1 (K), R132.1, U57.5 (FB)
unnamed: C117.2, D57.2 (A), L57.2
unnamed: D57.1 (K), R133.1, U58.5 (FB)
unnamed: C118.2, D58.1 (A), L58.2
unnamed: D58.2 (K), R134.1, U59.5 (FB)
unnamed: C119.2, D59.1 (A), L59.2
unnamed: D59.2 (K), R135.1, U60.5 (FB)
unnamed: C120.2, D60.1 (A), L60.2
unnamed: D60.2 (K), R136.1, U61.5 (FB)
unnamed: C126.2, D61.2 (A), L61.2
unnamed: D61.1 (K), R142.1, U62.5 (FB)
unnamed: C127.2, D62.2 (A), L62.2
unnamed: D62.1 (K), R143.1, U63.5 (FB)
unnamed: C128.2, D63.1 (A), L63.2
unnamed: D63.2 (K), R144.1, U64.5 (FB)
unnamed: C129.2, D64.2 (A), L64.2
unnamed: D64.1 (K), R145.1, U65.5 (FB)
unnamed: C130.2, D65.2 (A), L65.2
unnamed: D65.1 (K), R146.1, U66.5 (FB)
unnamed: C136.2, D66.2 (A), L66.2
unnamed: D66.1 (K), R152.1, U67.5 (FB)
unnamed: C137.2, D67.2 (A), L67.2
unnamed: D67.1 (K), R153.1, U68.5 (FB)
unnamed: C138.2, D68.2 (A), L68.2
unnamed: D68.1 (K), R154.1, U69.5 (FB)
unnamed: C139.2, D69.2 (A), L69.2
unnamed: D69.1 (K), R155.1, U70.5 (FB)
unnamed: C140.2, D70.2 (A), L70.2
unnamed: D70.1 (K), R156.1, U71.5 (FB)
unnamed: C146.2, D71.2 (A), L71.2
unnamed: D71.1 (K), R162.1, U72.5 (FB)
unnamed: C147.2, D72.2 (A), L72.2
unnamed: D72.1 (K), R163.1, U73.5 (FB)
unnamed: C148.2, D73.1 (A), L73.2
unnamed: D73.2 (K), R164.1, U74.5 (FB)
unnamed: C149.2, D74.1 (A), L74.2
unnamed: D74.2 (K), R165.1, U75.5 (FB)
unnamed: C150.2, D75.1 (A), L75.2
unnamed: D75.2 (K), R166.1, U76.5 (FB)
unnamed: C156.2, D76.2 (A), L76.2
unnamed: D76.1 (K), R172.1, U77.5 (FB)
unnamed: C157.2, D77.2 (A), L77.2
unnamed: D77.1 (K), R173.1, U78.5 (FB)
unnamed: C158.2, D78.1 (A), L78.2
unnamed: D78.2 (K), R174.1, U79.5 (FB)
unnamed: C159.2, D79.2 (A), L79.2
unnamed: D79.1 (K), R175.1, U80.5 (FB)
unnamed: C160.2, D80.2 (A), L80.2
unnamed: D80.1 (K), R176.1, U81.5 (FB)
unnamed: C166.2, D81.2 (A), L81.2
unnamed: D81.1 (K), R182.1, U82.5 (FB)
unnamed: C167.2, D82.2 (A), L82.2
unnamed: D82.1 (K), R183.1, U83.5 (FB)
unnamed: C168.2, D83.2 (A), L83.2
unnamed: D83.1 (K), R184.1, U84.5 (FB)
unnamed: C169.2, D84.2 (A), L84.2
unnamed: D84.1 (K), R185.1, U85.5 (FB)
unnamed: C170.2, D85.2 (A), L85.2
unnamed: D85.1 (K), R186.1, U86.5 (FB)
unnamed: C176.2, D86.2 (A), L86.2
unnamed: D86.1 (K), R192.1, U87.5 (FB)
unnamed: C177.2, D87.2 (A), L87.2
unnamed: D87.1 (K), R193.1, U88.5 (FB)
unnamed: C178.2, D88.1 (A), L88.2
unnamed: D88.2 (K), R194.1, U89.5 (FB)
unnamed: C179.2, D89.1 (A), L89.2
unnamed: D89.2 (K), R195.1, U90.5 (FB)
unnamed: C180.2, D90.1 (A), L90.2
unnamed: D90.2 (K), R196.1, U91.5 (FB)
unnamed: C186.2, D91.2 (A), L91.2
unnamed: D91.1 (K), R202.1, U92.5 (FB)
unnamed: C187.2, D92.2 (A), L92.2
unnamed: D92.1 (K), R203.1, U93.5 (FB)
unnamed: C188.2, D93.1 (A), L93.2
unnamed: D93.2 (K), R204.1, U94.5 (FB)
unnamed: C189.2, D94.2 (A), L94.2
unnamed: D94.1 (K), R205.1, U95.5 (FB)
unnamed: C190.2, D95.2 (A), L95.2
unnamed: D95.1 (K), R206.1, U96.5 (FB)
unnamed: C196.2, D96.2 (A), L96.2
unnamed: D96.1 (K), R212.1, U97.5 (FB)
unnamed: C197.2, D97.2 (A), L97.2
unnamed: D97.1 (K), R213.1, U98.5 (FB)
unnamed: C198.2, D98.2 (A), L98.2
unnamed: D98.1 (K), R214.1, U99.5 (FB)
unnamed: C199.2, D99.2 (A), L99.2
unnamed: D99.1 (K), R215.1, U100.5 (FB)
unnamed: C200.2, D100.2 (A), L100.2
unnamed: D100.1 (K), R216.1, U101.5 (FB)
unnamed: C206.2, D101.2 (A), L101.2
unnamed: D101.1 (K), R222.1, U102.5 (FB)
unnamed: C207.2, D102.2 (A), L102.2
unnamed: D102.1 (K), R223.1, U103.5 (FB)
unnamed: C208.2, D103.1 (A), L103.2
unnamed: D103.2 (K), R224.1, U104.5 (FB)
unnamed: C209.2, D104.1 (A), L104.2
unnamed: D104.2 (K), R225.1, U105.5 (FB)
unnamed: C210.2, D105.1 (A), L105.2
unnamed: D105.2 (K), R226.1, U106.5 (FB)
unnamed: C216.2, D106.2 (A), L106.2
unnamed: D106.1 (K), R232.1, U107.5 (FB)
unnamed: C217.2, D107.2 (A), L107.2
unnamed: D107.1 (K), R233.1, U108.5 (FB)
unnamed: C218.2, D108.1 (A), L108.2
unnamed: D108.2 (K), R234.1, U109.5 (FB)
unnamed: C219.2, D109.2 (A), L109.2
unnamed: D109.1 (K), R235.1, U110.5 (FB)
unnamed: C220.2, D110.2 (A), L110.2
unnamed: D110.1 (K), R236.1, U111.5 (FB)
unnamed: C226.2, D111.2 (A), L111.2
unnamed: D111.1 (K), R242.1, U112.5 (FB)
unnamed: C227.2, D112.2 (A), L112.2
unnamed: D112.1 (K), R243.1, U113.5 (FB)
unnamed: C228.2, D113.2 (A), L113.2
unnamed: D113.1 (K), R244.1, U114.5 (FB)
unnamed: C229.2, D114.2 (A), L114.2
unnamed: D114.1 (K), R245.1, U115.5 (FB)
unnamed: C230.2, D115.2 (A), L115.2
unnamed: D115.1 (K), R246.1, U116.5 (FB)
unnamed: C236.2, D116.2 (A), L116.2
unnamed: D116.1 (K), R252.1, U117.5 (FB)
unnamed: C237.2, D117.2 (A), L117.2
unnamed: D117.1 (K), R253.1, U118.5 (FB)
unnamed: C238.2, D118.1 (A), L118.2
unnamed: D118.2 (K), R254.1, U119.5 (FB)
unnamed: C239.2, D119.1 (A), L119.2
unnamed: D119.2 (K), R255.1, U120.5 (FB)
unnamed: C240.2, D120.1 (A), L120.2
unnamed: D120.2 (K), R256.1, U121.5 (FB)
unnamed: Q1.3 (D), U1.39 (VSYS)
unnamed: Q1.1 (G), U1.40 (VBUS)
unnamed: Q2.3 (C), Q6.1 (G), R1.2
unnamed: Q3.3 (C), Q7.1 (G), R3.2
unnamed: Q4.3 (C), Q8.1 (G), R5.2
unnamed: Q5.3 (C), Q9.1 (G), R7.2
unnamed: Q10.3 (C), Q14.1 (G), R9.2
unnamed: Q11.3 (C), Q15.1 (G), R11.2
unnamed: Q12.3 (C), Q16.1 (G), R13.2
unnamed: Q13.3 (C), Q17.1 (G), R15.2
unnamed: L1.1, U2.3 (SW)
unnamed: L2.1, U3.3 (SW)
unnamed: L3.1, U4.3 (SW)
unnamed: L4.1, U5.3 (SW)
unnamed: L5.1, U6.3 (SW)
unnamed: L6.1, U7.3 (SW)
unnamed: L7.1, U8.3 (SW)
unnamed: L8.1, U9.3 (SW)
unnamed: L9.1, U10.3 (SW)
unnamed: L10.1, U11.3 (SW)
unnamed: L11.1, U12.3 (SW)
unnamed: L12.1, U13.3 (SW)
unnamed: L13.1, U14.3 (SW)
unnamed: L14.1, U15.3 (SW)
unnamed: L15.1, U16.3 (SW)
unnamed: L16.1, U17.3 (SW)
unnamed: L17.1, U18.3 (SW)
unnamed: L18.1, U19.3 (SW)
unnamed: L19.1, U20.3 (SW)
unnamed: L20.1, U21.3 (SW)
unnamed: L21.1, U22.3 (SW)
unnamed: L22.1, U23.3 (SW)
unnamed: L23.1, U24.3 (SW)
unnamed: L24.1, U25.3 (SW)
unnamed: L25.1, U26.3 (SW)
unnamed: L26.1, U27.3 (SW)
unnamed: L27.1, U28.3 (SW)
unnamed: L28.1, U29.3 (SW)
unnamed: L29.1, U30.3 (SW)
unnamed: L30.1, U31.3 (SW)
unnamed: L31.1, U32.3 (SW)
unnamed: L32.1, U33.3 (SW)
unnamed: L33.1, U34.3 (SW)
unnamed: L34.1, U35.3 (SW)
unnamed: L35.1, U36.3 (SW)
unnamed: L36.1, U37.3 (SW)
unnamed: L37.1, U38.3 (SW)
unnamed: L38.1, U39.3 (SW)
unnamed: L39.1, U40.3 (SW)
unnamed: L40.1, U41.3 (SW)
unnamed: L41.1, U42.3 (SW)
unnamed: L42.1, U43.3 (SW)
unnamed: L43.1, U44.3 (SW)
unnamed: L44.1, U45.3 (SW)
unnamed: L45.1, U46.3 (SW)
unnamed: L46.1, U47.3 (SW)
unnamed: L47.1, U48.3 (SW)
unnamed: L48.1, U49.3 (SW)
unnamed: L49.1, U50.3 (SW)
unnamed: L50.1, U51.3 (SW)
unnamed: L51.1, U52.3 (SW)
unnamed: L52.1, U53.3 (SW)
unnamed: L53.1, U54.3 (SW)
unnamed: L54.1, U55.3 (SW)
unnamed: L55.1, U56.3 (SW)
unnamed: L56.1, U57.3 (SW)
unnamed: L57.1, U58.3 (SW)
unnamed: L58.1, U59.3 (SW)
unnamed: L59.1, U60.3 (SW)
unnamed: L60.1, U61.3 (SW)
unnamed: L61.1, U62.3 (SW)
unnamed: L62.1, U63.3 (SW)
unnamed: L63.1, U64.3 (SW)
unnamed: L64.1, U65.3 (SW)
unnamed: L65.1, U66.3 (SW)
unnamed: L66.1, U67.3 (SW)
unnamed: L67.1, U68.3 (SW)
unnamed: L68.1, U69.3 (SW)
unnamed: L69.1, U70.3 (SW)
unnamed: L70.1, U71.3 (SW)
unnamed: L71.1, U72.3 (SW)
unnamed: L72.1, U73.3 (SW)
unnamed: L73.1, U74.3 (SW)
unnamed: L74.1, U75.3 (SW)
unnamed: L75.1, U76.3 (SW)
unnamed: L76.1, U77.3 (SW)
unnamed: L77.1, U78.3 (SW)
unnamed: L78.1, U79.3 (SW)
unnamed: L79.1, U80.3 (SW)
unnamed: L80.1, U81.3 (SW)
unnamed: L81.1, U82.3 (SW)
unnamed: L82.1, U83.3 (SW)
unnamed: L83.1, U84.3 (SW)
unnamed: L84.1, U85.3 (SW)
unnamed: L85.1, U86.3 (SW)
unnamed: L86.1, U87.3 (SW)
unnamed: L87.1, U88.3 (SW)
unnamed: L88.1, U89.3 (SW)
unnamed: L89.1, U90.3 (SW)
unnamed: L90.1, U91.3 (SW)
unnamed: L91.1, U92.3 (SW)
unnamed: L92.1, U93.3 (SW)
unnamed: L93.1, U94.3 (SW)
unnamed: L94.1, U95.3 (SW)
unnamed: L95.1, U96.3 (SW)
unnamed: L96.1, U97.3 (SW)
unnamed: L97.1, U98.3 (SW)
unnamed: L98.1, U99.3 (SW)
unnamed: L99.1, U100.3 (SW)
unnamed: L100.1, U101.3 (SW)
unnamed: L101.1, U102.3 (SW)
unnamed: L102.1, U103.3 (SW)
unnamed: L103.1, U104.3 (SW)
unnamed: L104.1, U105.3 (SW)
unnamed: L105.1, U106.3 (SW)
unnamed: L106.1, U107.3 (SW)
unnamed: L107.1, U108.3 (SW)
unnamed: L108.1, U109.3 (SW)
unnamed: L109.1, U110.3 (SW)
unnamed: L110.1, U111.3 (SW)
unnamed: L111.1, U112.3 (SW)
unnamed: L112.1, U113.3 (SW)
unnamed: L113.1, U114.3 (SW)
unnamed: L114.1, U115.3 (SW)
unnamed: L115.1, U116.3 (SW)
unnamed: L116.1, U117.3 (SW)
unnamed: L117.1, U118.3 (SW)
unnamed: L118.1, U119.3 (SW)
unnamed: L119.1, U120.3 (SW)
unnamed: L120.1, U121.3 (SW)

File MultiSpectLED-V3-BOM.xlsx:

Item | Reference | Qty | Value | Description | Manufacturer Part Number
1 | C1,C2,C3,C4,C5,C11,C12,C13,C14,C15,C21,C22,C23,C24,C25,C31,C32,C33,C34,C35,C41,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 | 120 | 10uF | CAP CER 10UF 16V X5R 0805 | GRM21BR61C106KE15L
2 | C6,C7,C8,C9,C10,C16,C17,C18,C19,C20,C26,C27,C28,C29,C30,C36,C37,C38,C39,C40,C46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 | 120 | 1uF | CAP CER 1UF 16V X5R 0805 | GRM21BR61C105KA01L
3 | D1,D16,D31,D46,D61,D76,D91,D106 | 8 | 280nm | LED, UV, 270nm | XBT-3535-UV-A130-CD270-00
4 | D2,D17,D32,D47,D62,D77,D92,D107 | 8 | 367nm | LED, UV, 367nm | CUN6GF1A
5 | D3,D18,D33,D48,D63,D78,D93,D108 | 8 | 405nm | LED, UV, 405nm | ELUA3535OGB-P0010U23240500-VD1M
6 | D4,D19,D34,D49,D64,D79,D94,D109 | 8 | 448nm | LED, VIS, 448nm, Blue | LXML-PR01-0500
7 | D5,D20,D35,D50,D65,D80,D95,D110 | 8 | 470nm | LED, VIS, 470nm, Blue | LXML-PB01-0040
8 | D6,D21,D36,D51,D66,D81,D96,D111 | 8 | 505nm | LED, VIS, 505nm, Cyan | LXML-PE01-0070
9 | D7,D22,D37,D52,D67,D82,D97,D112 | 8 | 530nm | LED, VIS, 530nm, Green | LXML-PM01-0100
10 | D8,D23,D38,D53,D68,D83,D98,D113 | 8 | 568nm | LED, VIS, 568nm, Line | LXML-PX02-0000
11 | D9,D24,D39,D54,D69,D84,D99,D114 | 8 | 591nm | LED, VIS, 591nm, Amber | LXM2-PL01-0000
12 | D10,D25,D40,D55,D70,D85,D100,D115 | 8 | 617nm | LED, VIS, 617nm, Orange | LXM2-PH01-0070
13 | D11,D26,D41,D56,D71,D86,D101,D116 | 8 | 627nm | LED, VIS, 627nm, Red | LXM2-PD01-0050
14 | D12,D27,D42,D57,D72,D87,D102,D117 | 8 | 655nm | LED, VIS, 655nm, Red | LXM3-PD01
15 | D13,D28,D43,D58,D73,D88,D103,D118 | 8 | 740nm | LED, IR, 740nm | QBHP684-IR4BU
16 | D14,D29,D44,D59,D74,D89,D104,D119 | 8 | 850nm | LED, IR, 850nm | QBHP684U-IRU
17 | D15,D30,D45,D60,D75,D90,D105,D120 | 8 | 940nm | LED, IR, 940nm | QBHP684-IR1BU
18 | H1,H2,H3,H4 | 4 | M3 Mounting Hole | Mounting Hole | N/A
19 | J1 | 1 | Screw_Terminal_01x02 |  | 393900102
20 | L1,L2,L3,L4,L5,L6,L7,L8,L9,L10,L11,L12,L13,L14,L15,L16,L17,L18,L19,L20,L21,L22,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 | 120 | 4.7u | FIXED IND 4.7UH 920MA 260MOHM SM | CBC2518T4R7M
21 | Q1,Q6,Q7,Q8,Q9,Q14,Q15,Q16,Q17 | 9 | DMG2301L | -3A Id, -20V Vds, P-Channel MOSFET, SOT-23 | DMG2301L-7
22 | Q2,Q3,Q4,Q5,Q10,Q11,Q12,Q13 | 8 | BC817 | 0.8A Ic, 45V Vce, NPN Transistor, SOT-23 | BC817-40-7-F
23 | R1,R2,R3,R4,R5,R6,R7,R8,R9,R10,R11,R12,R13,R14,R15,R16,R17,R18,R19,R20,R21,R27,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 | 136 | 100K | RES 100K OHM 1% 1/3W 0805 | CRGH0805F100K
24 | R22,R23,R24,R25,R26,R32,R33,R34,R35,R36,R42,R43,R44,R45,R46,R52,R53,R54,R55,R56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 | 120 | 0.2 | RES 0.2 OHM 1% 1/3W 0805 | RL1220S-R20-F
25 | U1 | 1 | RaspberryPi_Pico2_SM | RASPBERRY PI PICO 2 WH RP2350 | SC1634
26 | U2,U3,U4,U5,U6,U7,U8,U9,U10,U11,U12,U13,U14,U15,U16,U17,U18,U19,U20,U21,U22,U23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 | 120 | PAM2804 | IC LED DRIVER RGLTR 1A TSOT25 | PAM2804AAB010
27
28
